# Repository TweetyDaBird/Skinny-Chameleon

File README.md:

# The Skinny Chameleon 

## Features
**The Skinny Chameleon is a grid type orthogonal keyboard with two optional layouts in one single PCB. It's a direct offshoot of the original Chameleon, only made to fit the Preonic's and Planck's non-standard key spacing.** Being able to break off the bottom row allows both a 5x12 layout acting as a replacement PCB for OLKB's Preonic and a 4x12 layout for the equally popular little brother Planck on the same PCB. 

Using the non-standard 19.00 mm grid spacing this PCB fit's all original cases for Preonic & Planck, and should fit all the various 'aftermarket' keyboard cases intended for these PCB's as well.

Being fully hot-swap and with PCB mounted stabilizers, Chameleon adds support for up to four encoders and a bottom row allowing either a single stabilized 2u key or two 2u keys in the middle, allowing for a layout that suits most users. If used as a 5 row keyboard, the bottom encoders can alternatively be placed at the edges on the second row, but **not more than one per corner.** 

The Chameleon features 8 bottomfacing RGB LEDs for underglow effects or to be used for layer indication or similar. 

**Please Note! This PCB fits original Planck/Preonic cases! NOT BM40/JJ40/JJ50!**

### Main Features:
* QMK and VIAL compatible, fully programmable keyboard**
* RP2040 MCU, Dual-core Arm Cortex M0+ processor, flexible clock running up to 133 MHz
* 264KB of SRAM, and 4MB of on-board Flash memory
* USB-C connector, (USB 1.1 device and host support)
* Low-power sleep and dormant modes
* Drag-and-drop programming using mass storage over USB
* Kaihl hot-swap sockets for Cherry MX compatible switches (3 & 5-pin)
* Cherry Style PCB mounted stabilizers
* Two main layouts:
	* 5x12 with 58 to 60 keys
	* 4x12 with 46 to 48 keys (Break off bottom row) 
* Configurable bottom row:
	* Full 1u grid
	* 1x centered, stabilized 2u key
	* 2x centered,  stabilized 2u keys

### Optional add-ons:
* Support for up to 4 rotary encoders **(one encoder per corner)**
* Optional RGB underglow (8x SK6812 mini-e)

## Assembly
**Little or no tools at all needed!** The PCB can be delivered fully soldered and ready to use, either as a full matrix, or with your selection of rotary encoders. If ordered fully soldered, the bottom row for the size specified (4x12/5x12) is soldered, and accepts both a full 1u grid and 2u keys without any changes.

**Or as a "DIY Kit" with some soldering needed**. As a DIY kit the hotswap sockets for the 6 encoder positions (corners) and the 2u keys are left unsoldered, and you can add them as your layout requires to corners not using an encoder, and to the bottom row you choose to use. (A total if 9 sockets included for soldering).

The optional RGB LED's needs to be soldered in place if used. (8 pcs, SK681x mini-E)

_The RGB LED's and encoders are all pre-soldered together with the required hotswap sockets at no extra cost, if the soldering option is selected and all parts needed are purchased in the same order._

# Case & Plate
**The design is made to fit any Planck or Preonic case and plate, and act as a drop-in replacement PCB.** It does *not* fit any case not advertised as specific fitment for these. 

**Any mounting hardware should accompany the case, and is not supplied with the PCB.** This means you will have to save and reuse the hardware with your originial case. 

**The solder on studs can be removed from your original PCB and re-used.**  Or, you can choose to buy replacement studs as an add-on, and not have to bother with the removal. Please note that the replacement studs are slightly loose in the holes to allow the use of both types, since the original ones are (possibly?) a speciality item made for OLKB, and I'm using the nearest off the shelf replacement, and they _absolutely need_ to be soldered on to the PCB to be useful. I highly suggest attaching them to the case, placing the PCB and solder as they are aligned.

***Change for version 1.10*** New PCB's are harder to fit the unusually sized original OLKB studs. Having to make a choice between the weird size making off the shelf studs be hard to center and re-using the original studs (which takes some skill), I'm choosing to make the off the shelf ones I can supply at a decent price easier to solder. 
# Making Chameleon yourself
**Chameleon is open source / open hardware, and can be manufactured by anyone. The release contains all the neccesary files like parts lists, positions files etc for a full PCB/SMT production.** 

The formatting and files are geared towards [JLCPCB](http://jlcpcb.com), but never tested as such, as I only manufacture the PCB then do the assembly myself (at least until this reaches a volume justifying full SMT production).

The components are small enough that you would have to be highly skilled to attempt to assemble this either as hand soldered, or small scale/DIY SMT. I would highly recommend ordering the PCB as fully assembled unless you know you have the neccesary skill-set.

## Buy a kit!
I sell complete kits, making it easy to build your keyboard, and it also supports prototypes for new wacky ones. 

## Discord for build help and discussions!

# License

[![CC BY-SA 4.0][cc-by-sa-shield]][cc-by-sa] - This work is licensed under a
[Creative Commons Attribution-ShareAlike 4.0 International License][cc-by-sa].

[cc-by-sa]: http://creativecommons.org/licenses/by-sa/4.0/
[cc-by-sa-shield]: https://img.shields.io/badge/License-CC%20BY--SA%204.0-lightgrey.svg

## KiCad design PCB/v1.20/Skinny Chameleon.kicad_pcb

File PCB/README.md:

# Chameleon PCB

## Change Log:
- v1.00 - Initial Release

- v1.10 - Second Release
  - Silkscreen correction
  
- v1.11 - Third Release
  - Correction of solder on stud pads (including PCB silkscreen to mark which are Planck/Preonic)
  
- v1.20 - Fourth Release
  - Pushed out USB connector
  - Refactored encoder footprints
  - Refactored switch footprints with reinforced pads(larger via).

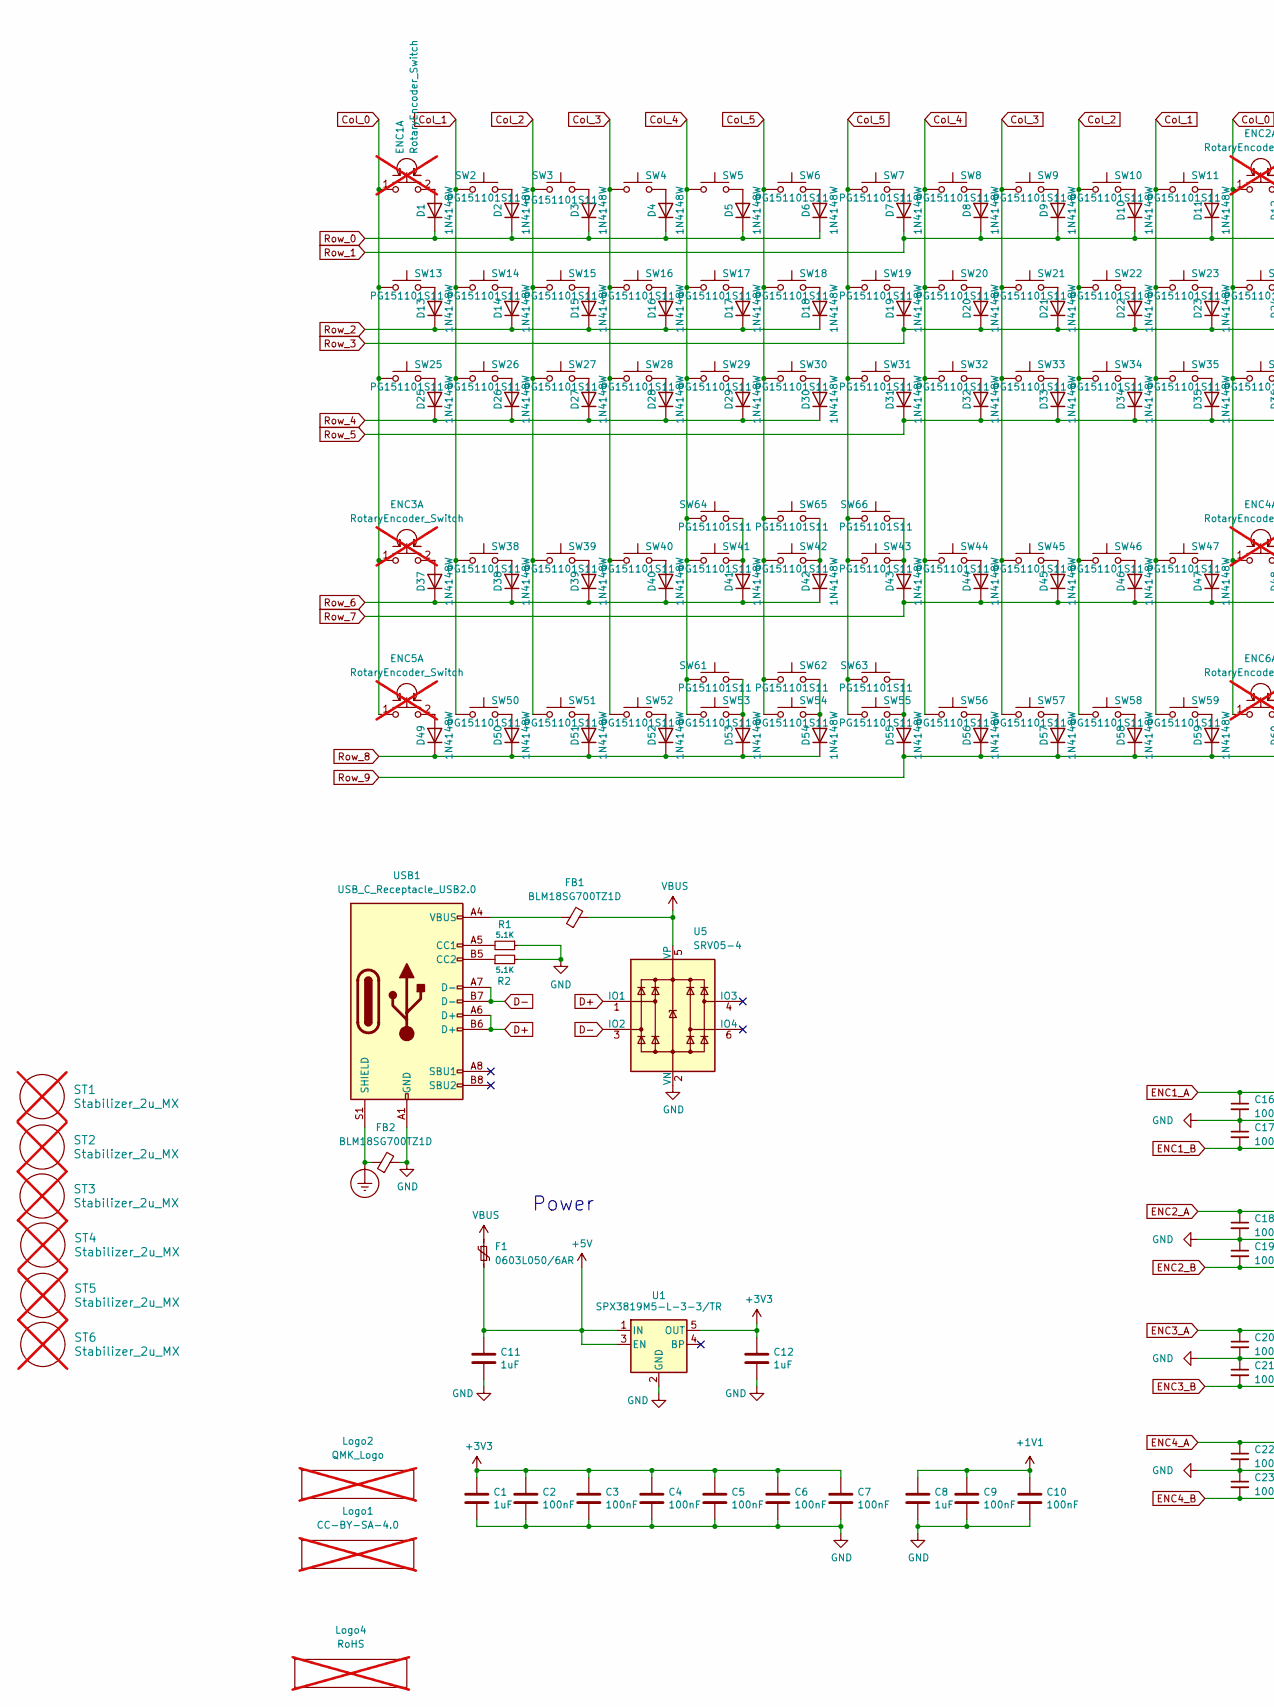
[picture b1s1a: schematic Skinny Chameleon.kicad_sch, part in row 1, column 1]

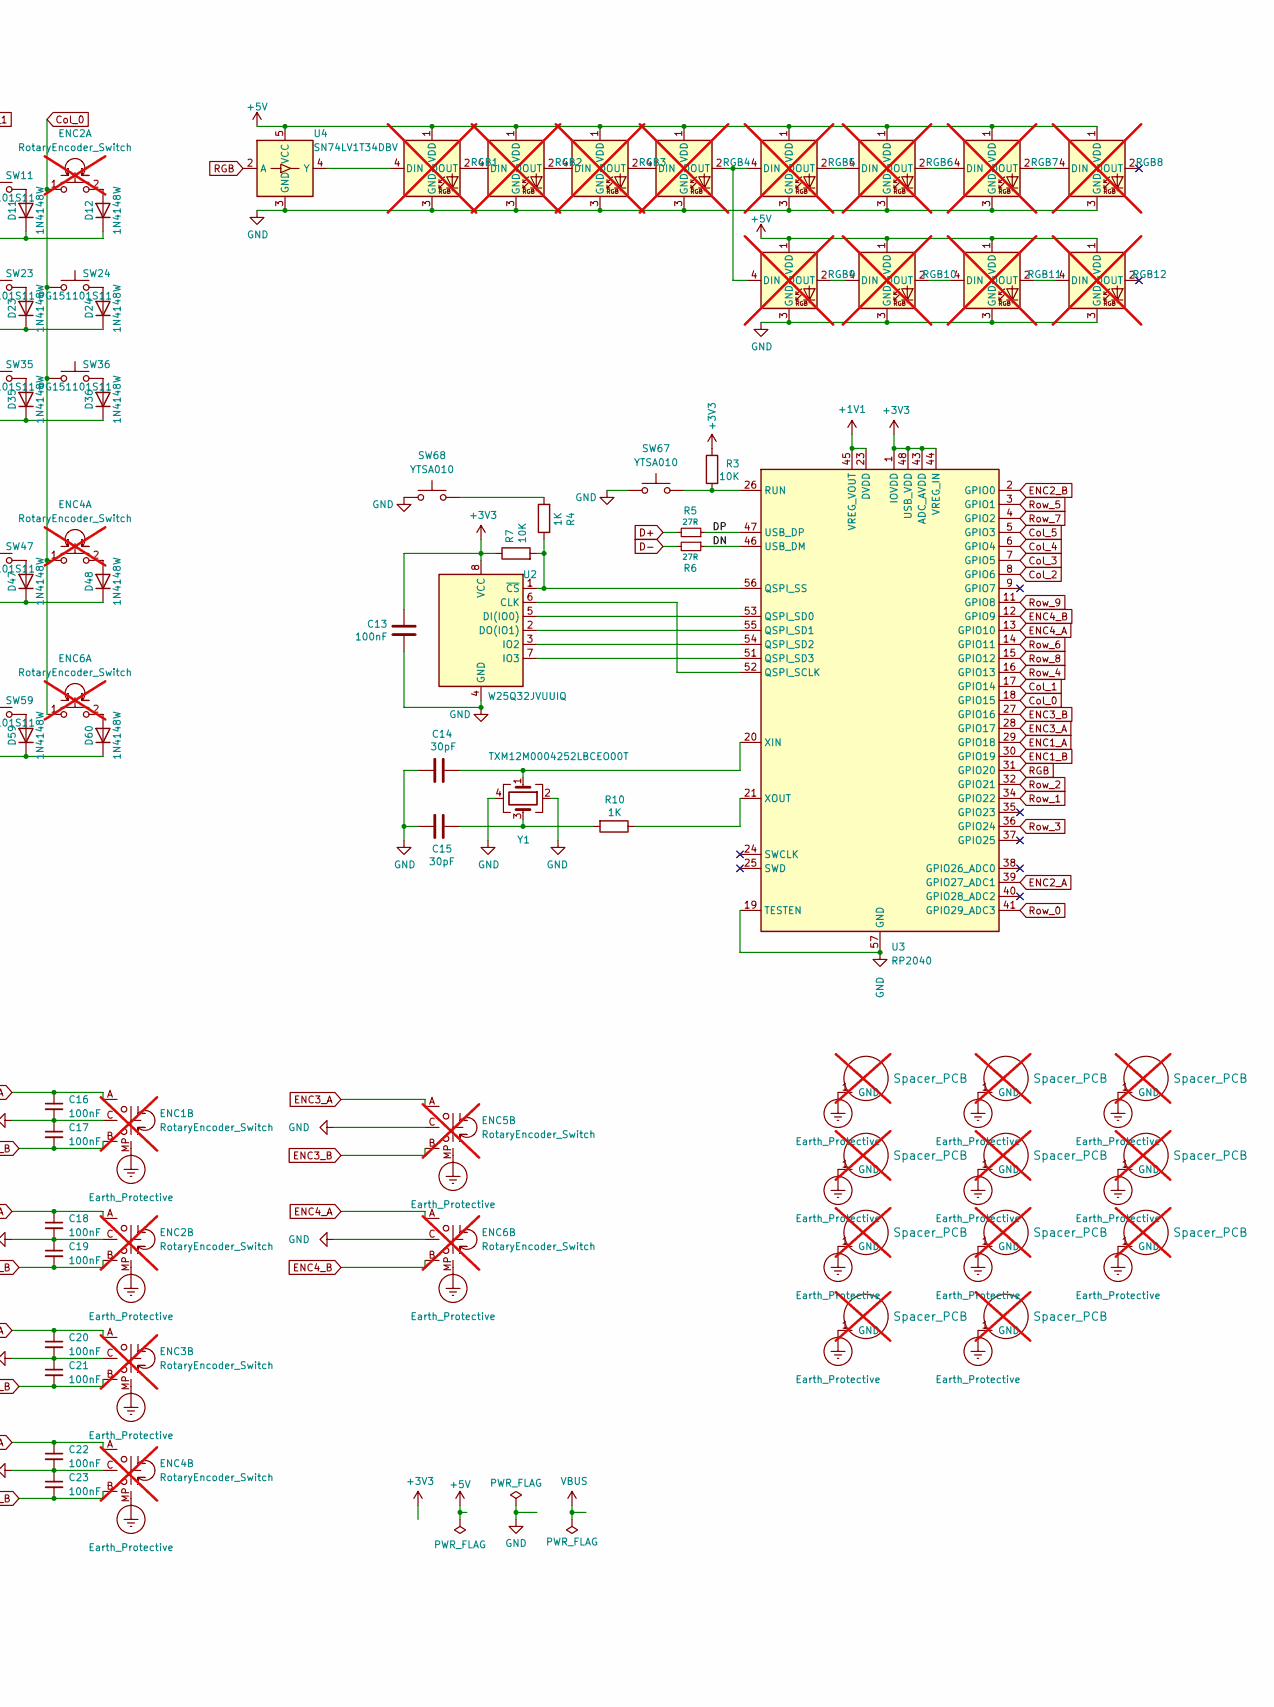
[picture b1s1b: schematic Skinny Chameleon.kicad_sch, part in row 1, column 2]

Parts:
C1, C8, C11, C12: 1uF; C_0402_1005Metric; LCSC Part # C52923
C2, C3, C4, C5, C6, C7, C9, C10, C13, C16, C17, C18, C19, C20, C21, C22, C23: 100nF; C_0402_1005Metric; LCSC Part # C1525
C14, C15: 30pF; C_0402_1005Metric; LCSC Part # C1570
D1, D2, D3, D4, D5, D6, D7, D8, D9, D10, D11, D12, D13, D14, D15, D16, D17, D18, D19, D20, D21, D22, D23, D24, D25, D26, D27, D28, D29, D30, D31, D32, D33, D34, D35, D36, D37, D38, D39, D40, D41, D42, D43, D44, D45, D46, D47, D48, D49, D50, D51, D52, D53, D54, D55, D56, D57, D58, D59, D60: 1N4148W; D_SOD-323; LCSC Part # C2128
ENC1, ENC2: RotaryEncoder_Switch; SW_MX_HotSwap_Encoder_reinforced; not fitted
ENC3, ENC4, ENC5, ENC6: RotaryEncoder_Switch; SW_MX_HotSwap_Encoder_inverted_reinforced; not fitted
F1: 0603L050/6AR; R_0603_1608Metric; LCSC Part # C163116
FB1, FB2: BLM18SG700TZ1D; C_0603_1608Metric_Pad1.08x0.95mm_HandSolder; LCSC Part # C1002
H1, H2, H4, H5, H6, H7, H9, H11, H12, H13, H14: Spacer_PCB; Planck Spacer; not fitted
Logo1: CC-BY-SA-4.0; CC_BY_SA_40_line; not fitted
Logo2: QMK_Logo; qmk logo; not fitted
Logo4: RoHS; RoHs; not fitted
R1, R2: 5.1K; R_0402_1005Metric; LCSC Part # C25905
R3, R7: 10K; R_0402_1005Metric; LCSC Part # C25744
R4, R10: 1K; R_0402_1005Metric; LCSC Part # C11702
R5, R6: 27R; R_0402_1005Metric; LCSC Part # C321419
RGB1, RGB2, RGB3, RGB4, RGB5, RGB6, RGB7, RGB8, RGB9, RGB10, RGB11, RGB12: SK6812MINI-E; RGB_SK6812MINI-E; not fitted
ST1, ST2, ST3, ST4, ST5, ST6: Stabilizer_2u_MX; Stabilizer_Cherry_MX_2.00u; not fitted
SW2, SW3, SW4, SW5, SW6, SW7, SW8, SW9, SW10, SW11, SW13, SW14, SW15, SW16, SW17, SW18, SW19, SW20, SW21, SW22, SW23, SW24, SW25, SW26, SW27, SW28, SW29, SW30, SW31, SW32, SW33, SW34, SW35, SW36, SW38, SW39, SW40, SW41, SW42, SW43, SW44, SW45, SW46, SW47, SW50, SW51, SW52, SW53, SW54, SW55, SW56, SW57, SW58, SW59, SW61, SW62, SW63, SW64, SW65, SW66: PG151101S11; SW_MX_HotSwap_reinforced; LCSC Part # C2803348
SW67, SW68: YTSA010; LCSC Part # C967783
U1: SPX3819M5-L-3-3/TR; SOT-23-5; LCSC Part # C9055
U2: W25Q32JVUUIQ; USON-8_4x3mm_P0.8mm; LCSC Part # C2999380
U3: RP2040; QFN-56-1EP_7x7mm_P0.4mm_EP3.2x3.2mm; LCSC Part # C2040
U4: SN74LV1T34DBV; SOT-23-5; LCSC Part # C100024
U5: SRV05-4; SOT-23-6; LCSC Part # C20615829
USB1: USB_C_Receptacle_USB2.0; HRO_TYPE-C-31-M-12; LCSC Part # C165948
Y1: TXM12M0004252LBCEO00T; Crystal_SMD_2520-4Pin_2.5x2.0mm; LCSC Part # C284156

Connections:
+1V1: C8.1, C9.1, C10.1, U3.23 (DVDD), U3.45 (VREG_VOUT), U3.50 (DVDD)
+3V3: C1.1, C2.1, C3.1, C4.1, C5.1, C6.1, C7.1, C12.1, C13.1, R3.1, R7.1, U1.5 (OUT), U2.8 (VCC), U3.1 (IOVDD), U3.10 (IOVDD), U3.22 (IOVDD), U3.33 (IOVDD), U3.42 (IOVDD), U3.43 (ADC_AVDD), U3.44 (VREG_IN), U3.48 (USB_VDD), U3.49 (IOVDD)
+5V: C11.1, F1.2, RGB1.1 (VDD), RGB2.1 (VDD), RGB3.1 (VDD), RGB4.1 (VDD), RGB5.1 (VDD), RGB6.1 (VDD), RGB7.1 (VDD), RGB8.1 (VDD), RGB9.1 (VDD), RGB10.1 (VDD), RGB11.1 (VDD), RGB12.1 (VDD), U1.1 (IN), U1.3 (EN), U4.5 (VCC)
/DN: R6.1, U3.46 (USB_DM)
/DP: R5.1, U3.47 (USB_DP)
Col_0: ENC1.1, ENC1.S1, ENC2.1, ENC2.S1, ENC3.1, ENC3.S1, ENC4.1, ENC4.S1, ENC5.1, ENC5.S1, ENC6.1, ENC6.S1, SW13.1, SW24.1, SW25.1, SW36.1, U3.18 (GPIO15)
Col_1: SW2.2, SW11.1, SW14.1, SW23.1, SW26.1, SW35.1, SW38.1, SW47.1, SW50.1, SW59.1, U3.17 (GPIO14)
Col_2: SW3.2, SW10.1, SW15.1, SW22.1, SW27.1, SW34.1, SW39.1, SW46.1, SW51.1, SW58.1, U3.8 (GPIO6)
Col_3: SW4.1, SW9.1, SW16.1, SW21.1, SW28.1, SW33.1, SW40.1, SW45.1, SW52.1, SW57.1, U3.7 (GPIO5)
Col_4: SW5.1, SW8.1, SW17.1, SW20.1, SW29.1, SW32.1, SW41.1, SW44.1, SW53.1, SW56.1, SW61.2, SW64.2, U3.6 (GPIO4)
Col_5: SW6.1, SW7.1, SW18.1, SW19.1, SW30.1, SW31.1, SW42.1, SW43.1, SW54.1, SW55.1, SW62.1, SW63.2, SW65.1, SW66.2, U3.5 (GPIO3)
D+: R5.2, U5.1 (IO1), USB1.A6 (D+), USB1.B6 (D+)
D-: R6.2, U5.3 (IO2), USB1.A7 (D-), USB1.B7 (D-)
ENC1_A: C16.1, ENC1.A, U3.29 (GPIO18)
ENC1_B: C17.2, ENC1.B, U3.30 (GPIO19)
ENC2_A: C18.1, ENC2.A, U3.39 (GPIO27_ADC1)
ENC2_B: C19.2, ENC2.B, U3.2 (GPIO0)
ENC3_A: C20.1, ENC3.A, ENC5.A, U3.28 (GPIO17)
ENC3_B: C21.2, ENC3.B, ENC5.B, U3.27 (GPIO16)
ENC4_A: C22.1, ENC4.A, ENC6.A, U3.13 (GPIO10)
ENC4_B: C23.2, ENC4.B, ENC6.B, U3.12 (GPIO9)
unnamed: C15.1, R10.2, Y1.3
unnamed: D1.2 (A), ENC1.2, ENC1.S2
unnamed: D2.2 (A), SW2.1
unnamed: D3.2 (A), SW3.1
unnamed: D4.2 (A), SW4.2
unnamed: D5.2 (A), SW5.2
unnamed: D6.2 (A), SW6.2
unnamed: D7.2 (A), SW7.2
unnamed: D8.2 (A), SW8.2
unnamed: D9.2 (A), SW9.2
unnamed: D10.2 (A), SW10.2
unnamed: D11.2 (A), SW11.2
unnamed: D12.2 (A), ENC2.2, ENC2.S2
unnamed: D13.2 (A), SW13.2
unnamed: D14.2 (A), SW14.2
unnamed: D15.2 (A), SW15.2
unnamed: D16.2 (A), SW16.2
unnamed: D17.2 (A), SW17.2
unnamed: D18.2 (A), SW18.2
unnamed: D19.2 (A), SW19.2
unnamed: D20.2 (A), SW20.2
unnamed: D21.2 (A), SW21.2
unnamed: D22.2 (A), SW22.2
unnamed: D23.2 (A), SW23.2
unnamed: D24.2 (A), SW24.2
unnamed: D25.2 (A), SW25.2
unnamed: D26.2 (A), SW26.2
unnamed: D27.2 (A), SW27.2
unnamed: D28.2 (A), SW28.2
unnamed: D29.2 (A), SW29.2
unnamed: D30.2 (A), SW30.2
unnamed: D31.2 (A), SW31.2
unnamed: D32.2 (A), SW32.2
unnamed: D33.2 (A), SW33.2
unnamed: D34.2 (A), SW34.2
unnamed: D35.2 (A), SW35.2
unnamed: D36.2 (A), SW36.2
unnamed: D37.2 (A), ENC3.2, ENC3.S2
unnamed: D38.2 (A), SW38.2
unnamed: D39.2 (A), SW39.2
unnamed: D40.2 (A), SW40.2
unnamed: D41.2 (A), SW41.2, SW64.1
unnamed: D42.2 (A), SW42.2, SW65.2
unnamed: D43.2 (A), SW43.2, SW66.1
unnamed: D44.2 (A), SW44.2
unnamed: D45.2 (A), SW45.2
unnamed: D46.2 (A), SW46.2
unnamed: D47.2 (A), SW47.2
unnamed: D48.2 (A), ENC4.2, ENC4.S2
unnamed: D49.2 (A), ENC5.2, ENC5.S2
unnamed: D50.2 (A), SW50.2
unnamed: D51.2 (A), SW51.2
unnamed: D52.2 (A), SW52.2
unnamed: D53.2 (A), SW53.2, SW61.1
unnamed: D54.2 (A), SW54.2, SW62.2
unnamed: D55.2 (A), SW55.2, SW63.1
unnamed: D56.2 (A), SW56.2
unnamed: D57.2 (A), SW57.2
unnamed: D58.2 (A), SW58.2
unnamed: D59.2 (A), SW59.2
unnamed: D60.2 (A), ENC6.2, ENC6.S2
unnamed: FB1.1, USB1.A4 (VBUS), USB1.A9 (VBUS), USB1.B4 (VBUS), USB1.B9 (VBUS)
unnamed: R4.2, SW68.2
unnamed: RGB1.4 (DIN), U4.4 (Y)
unnamed: RGB1.2 (DOUT), RGB2.4 (DIN)
unnamed: RGB2.2 (DOUT), RGB3.4 (DIN)
unnamed: RGB3.2 (DOUT), RGB4.4 (DIN)
unnamed: RGB4.2 (DOUT), RGB5.4 (DIN), RGB9.4 (DIN)
unnamed: RGB5.2 (DOUT), RGB6.4 (DIN)
unnamed: RGB6.2 (DOUT), RGB7.4 (DIN)
unnamed: RGB7.2 (DOUT), RGB8.4 (DIN)
unnamed: RGB9.2 (DOUT), RGB10.4 (DIN)
unnamed: RGB10.2 (DOUT), RGB11.4 (DIN)
unnamed: RGB11.2 (DOUT), RGB12.4 (DIN)
unnamed: U2.6 (CLK), U3.52 (QSPI_SCLK)
unnamed: U2.5 (DI(IO0)), U3.53 (QSPI_SD0)
unnamed: U2.2 (DO(IO1)), U3.55 (QSPI_SD1)
unnamed: U2.3 (IO2), U3.54 (QSPI_SD2)
unnamed: U2.7 (IO3), U3.51 (QSPI_SD3)
unnamed: R4.1, R7.2, U2.1 (~CS), U3.56 (QSPI_SS)
unnamed: R3.2, SW67.2, U3.26 (RUN)
unnamed: C14.1, U3.20 (XIN), Y1.1
unnamed: R10.1, U3.21 (XOUT)
unnamed: R1.2, USB1.A5 (CC1)
unnamed: R2.1, USB1.B5 (CC2)
RGB: U3.31 (GPIO20), U4.2 (A)
Row_0: D1.1 (K), D2.1 (K), D3.1 (K), D4.1 (K), D5.1 (K), D6.1 (K), U3.41 (GPIO29_ADC3)
Row_1: D7.1 (K), D8.1 (K), D9.1 (K), D10.1 (K), D11.1 (K), D12.1 (K), U3.34 (GPIO22)
Row_2: D13.1 (K), D14.1 (K), D15.1 (K), D16.1 (K), D17.1 (K), D18.1 (K), U3.32 (GPIO21)
Row_3: D19.1 (K), D20.1 (K), D21.1 (K), D22.1 (K), D23.1 (K), D24.1 (K), U3.36 (GPIO24)
Row_4: D25.1 (K), D26.1 (K), D27.1 (K), D28.1 (K), D29.1 (K), D30.1 (K), U3.16 (GPIO13)
Row_5: D31.1 (K), D32.1 (K), D33.1 (K), D34.1 (K), D35.1 (K), D36.1 (K), U3.3 (GPIO1)
Row_6: D37.1 (K), D38.1 (K), D39.1 (K), D40.1 (K), D41.1 (K), D42.1 (K), U3.14 (GPIO11)
Row_7: D43.1 (K), D44.1 (K), D45.1 (K), D46.1 (K), D47.1 (K), D48.1 (K), U3.4 (GPIO2)
Row_8: D49.1 (K), D50.1 (K), D51.1 (K), D52.1 (K), D53.1 (K), D54.1 (K), U3.15 (GPIO12)
Row_9: D55.1 (K), D56.1 (K), D57.1 (K), D58.1 (K), D59.1 (K), D60.1 (K), U3.11 (GPIO8)
VBUS: F1.1, FB1.2, U5.5 (VP)

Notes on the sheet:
Power

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
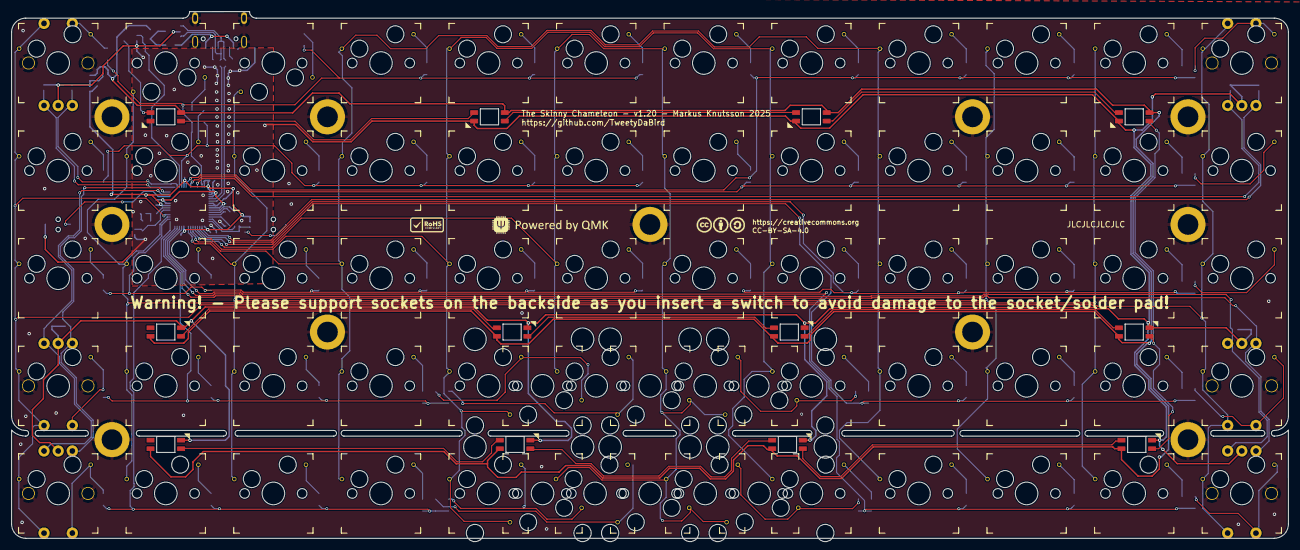
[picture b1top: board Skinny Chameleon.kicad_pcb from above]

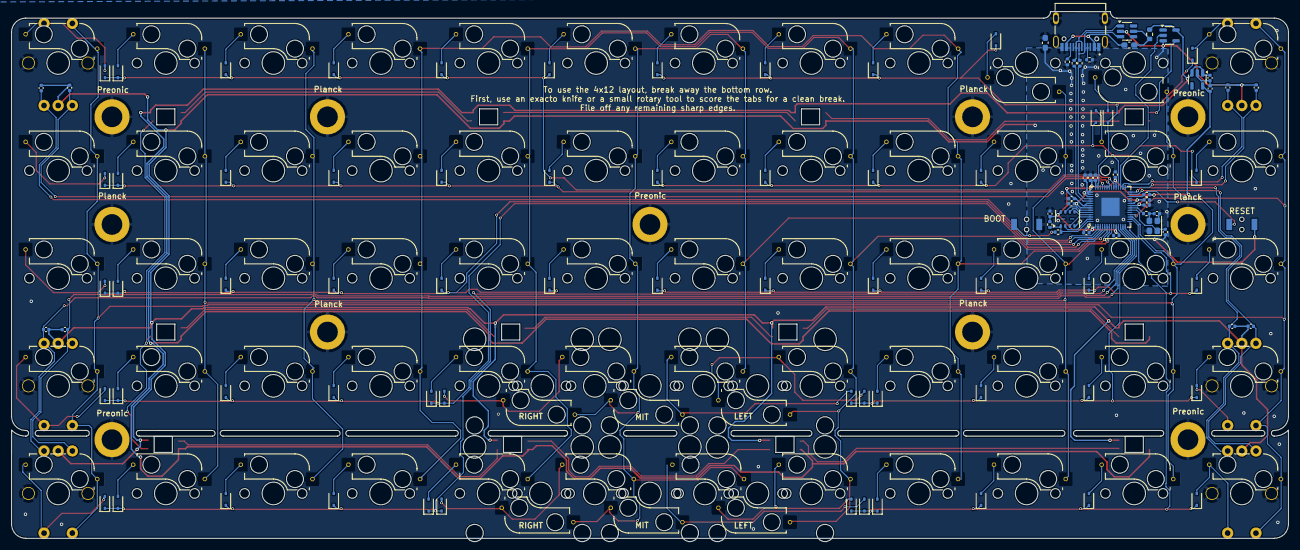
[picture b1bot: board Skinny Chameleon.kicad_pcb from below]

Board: 2 copper layers, 225.4 x 93.0 mm, 201 parts (115 on the bottom side), 120 nets.

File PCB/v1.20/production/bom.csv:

Designator,Footprint,Quantity,Value,LCSC Part #
"C1, C11, C12, C8",0402,4,1uF,C52923
"C10, C13, C16, C17, C18, C19, C2, C20, C21, C22, C23, C3, C4, C5, C6, C7, C9",0402,17,100nF,C1525
"C14, C15",0402,2,30pF,C1570
"D1, D10, D11, D12, D13, D14, D15, D16, D17, D18, D19, D2, D20, D21, D22, D23, D24, D25, D26, D27, D28, D29, D3, D30, D31, D32, D33, D34, D35, D36, D37, D38, D39, D4, D40, D41, D42, D43, D44, D45, D46, D47, D48, D49, D5, D50, D51, D52, D53, D54, D55, D56, D57, D58, D59, D6, D60, D7, D8, D9",D_SOD-323,60,1N4148W,C2128
F1,0603,1,0603L050/6AR,C163116
"FB1, FB2",0603,2,BLM18SG700TZ1D,C1002
"R1, R2",0402,2,5.1K,C25905
"R10, R4",0402,2,1K,C11702
"R3, R7",0402,2,10K,C25744
"R5, R6",0402,2,27R,C321419
"SW10, SW11, SW13, SW14, SW15, SW16, SW17, SW18, SW19, SW2, SW20, SW21, SW22, SW23, SW24, SW25, SW26, SW27, SW28, SW29, SW3, SW30, SW31, SW32, SW33, SW34, SW35, SW36, SW38, SW39, SW4, SW40, SW41, SW42, SW43, SW44, SW45, SW46, SW47, SW5, SW50, SW51, SW52, SW53, SW54, SW55, SW56, SW57, SW58, SW59, SW6, SW61, SW62, SW63, SW64, SW65, SW66, SW7, SW8, SW9",SW_MX_HotSwap_reinforced,60,PG151101S11,C2803348
"SW67, SW68",YTSA010,2,YTSA010,C967783
U1,SOT-23-5,1,SPX3819M5-L-3-3/TR,C9055
U2,USON-8_4x3mm_P0.8mm,1,W25Q32JVUUIQ,C2999380
U3,QFN-56-1EP_7x7mm_P0.4mm_EP3.2x3.2mm,1,RP2040,C2040
U4,SOT-23-5,1,SN74LV1T34DBV,C100024
U5,SOT-23-6,1,SRV05-4,C20615829
USB1,HRO_TYPE-C-31-M-12,1,USB_C_Receptacle_USB2.0,C165948
Y1,Crystal_SMD_2520-4Pin_2.5x2.0mm,1,TXM12M0004252LBCEO00T,C284156

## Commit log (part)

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2024-08-19 Skinny Chameleon v1.00
    Initial design
2024-08-19 Skinny Chameleon v 1.10
    - Corrected mounting hole position for Planck layout
    - Smaller hole on solder ring for spacers
    - Re-centered USB port.
2025-03-25 Skinny Chameleon v1.11
2025-08-01 V1.11
    Corrections to silkscreen.
    Marking the spacer mounting holes for Planck/Preonic
    Marking Sockets for layout.
    Added socket warning.
    Add RoHS marking.
2025-11-29 Added plate for Skinny Chameleon & BLE
    Moved folders around
2025-11-29 Added v 1.20
    - Moved USB out for better case fitment.
    - Added via's for pad reinforment.

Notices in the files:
PCB/v1.11/Skinny Chameleon.kicad_sch:
Licensed under Creative Commons BY-SA 4.0 International
